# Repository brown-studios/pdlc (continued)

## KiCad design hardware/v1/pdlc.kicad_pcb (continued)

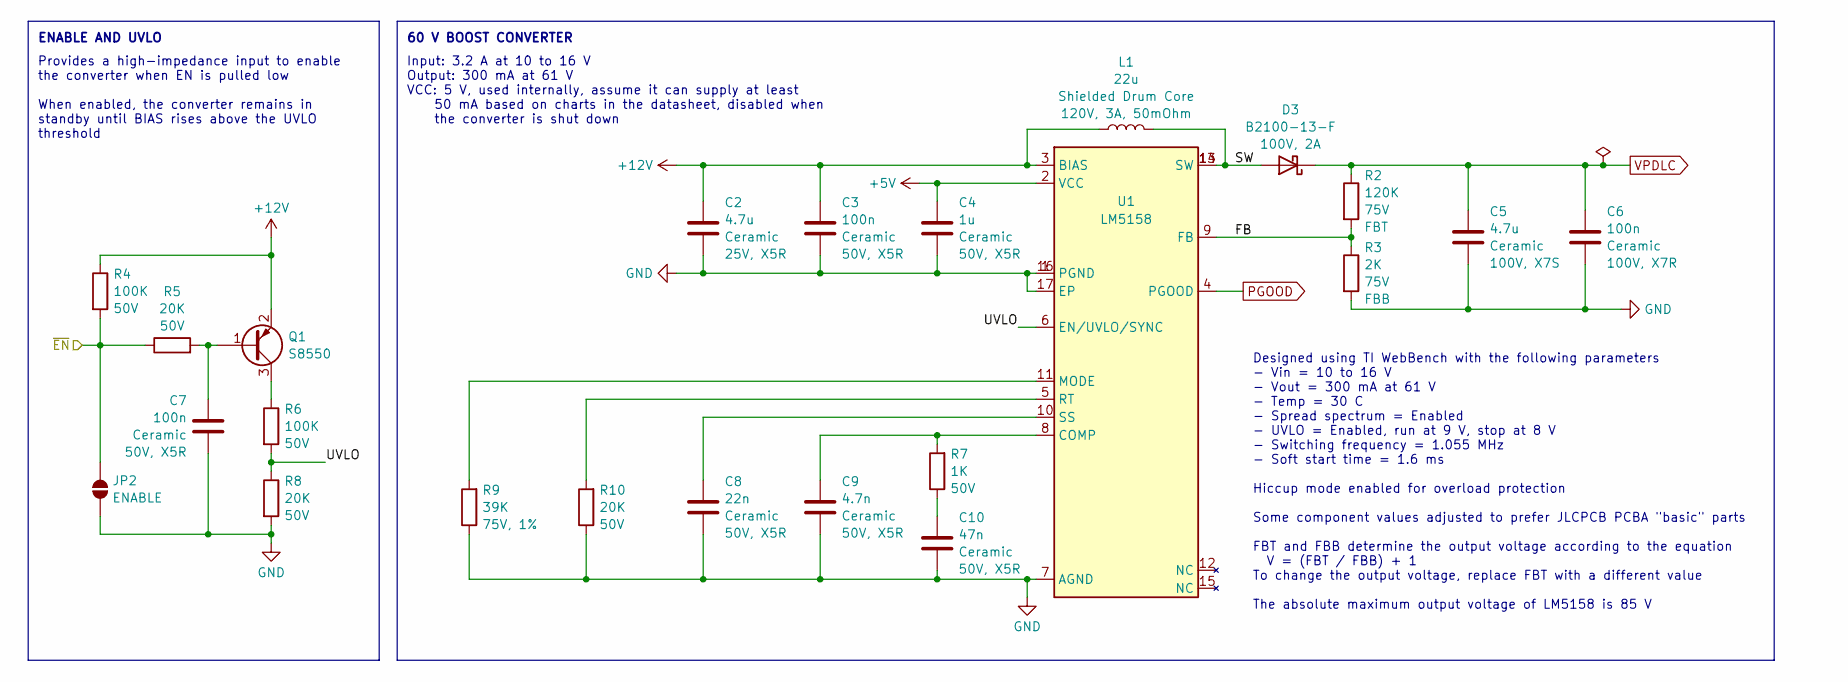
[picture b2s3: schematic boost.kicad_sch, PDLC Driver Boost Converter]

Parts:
C2: 4.7u; C_0805_2012Metric; Rating 25V, X5R; LCSC C1779
C3: 100n; C_0603_1608Metric; Rating 50V, X5R; LCSC C14663
C4: 1u; C_0603_1608Metric; Rating 50V, X5R; LCSC C15849
C5: 4.7u; C_1210_3225Metric; Rating 100V, X7S; LCSC C2803397
C6: 100n; C_0805_2012Metric; Rating 100V, X7R; LCSC C28233
C7: 100n; C_0402_1005Metric; Rating 50V, X5R; LCSC C307331
C8: 22n; C_0402_1005Metric; Rating 50V, X5R; LCSC C1532
C9: 4.7n; C_0402_1005Metric; Rating 50V, X5R; LCSC C1538
C10: 47n; C_0603_1608Metric; Rating 50V, X5R; LCSC C1622
D3: B2100-13-F; D_SMB; Rating 100V, 2A; LCSC C110479
JP2: SolderJumper_2_Open; SolderJumper-2_P1.3mm_Open_TrianglePad1.0x1.5mm
L1: 22u; WE-PD_1050P; Rating 120V, 3A, 50mOhm; Part 7447714220; LCSC C2651173
Q1: S8550; SOT-23; LCSC C105432
R2: 120K; R_0603_1608Metric; Rating 75V; LCSC C25808
R3: 2K; R_0603_1608Metric; Rating 75V; LCSC C22975
R4, R6: 100K; R_0402_1005Metric; Rating 50V; LCSC C25741
R5, R8, R10: 20K; R_0402_1005Metric; Rating 50V; LCSC C25765
R7: 1K; R_0402_1005Metric; Rating 50V; LCSC C11702
R9: 39K; R_0603_1608Metric; Rating 75V, 1%; LCSC C23153
U1: LM5158; LCSC C3188433

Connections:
+5V: C4.1, U1.2 (VCC); also elsewhere on the board
+12V: C2.1, C3.1, L1.1, Q1.2 (E), R4.1, U1.3 (BIAS); also elsewhere on the board
/boost/FB: R2.2, R3.1, U1.9 (FB)
/boost/SW: D3.2 (A), L1.2, U1.13 (SW), U1.14 (SW)
/boost/UVLO: R6.2, R8.1, U1.6 (EN/UVLO/SYNC)
/~EN: JP2.1 (A), R4.2, R5.1; also elsewhere on the board
GND: C2.2, C3.2, C4.2, C5.2, C6.2, C7.2, C8.2, C9.2, C10.2, JP2.2 (B), R3.2, R8.2, R9.1, R10.1, U1.1 (PGND), U1.7 (AGND), U1.16 (PGND), U1.17 (EP); also elsewhere on the board
unnamed: C10.1, R7.1
unnamed: C7.1, Q1.1 (B), R5.2
unnamed: Q1.3 (C), R6.1
unnamed: C9.1, R7.2, U1.8 (COMP)
unnamed: R9.2, U1.11 (MODE)
unnamed: R10.2, U1.5 (RT)
unnamed: C8.1, U1.10 (SS)
PGOOD: U1.4 (PGOOD); also elsewhere on the board
VPDLC: C5.1, C6.1, D3.1 (K), R2.1; also elsewhere on the board

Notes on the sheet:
60 V BOOST CONVERTER
Provides a high-impedance input to enable the converter when EN is pulled low When enabled, the converter remains in standby until BIAS rises above the UVLO threshold
Designed using TI WebBench with the following parameters - Vin = 10 to 16 V - Vout = 300 mA at 61 V - Temp = 30 C - Spread spectrum = Enabled - UVLO = Enabled, run at 9 V, stop at 8 V - Switching frequency = 1.055 MHz - Soft start time = 1.6 ms Hiccup mode enabled for overload protection Some compo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
ENABLE AND UVLO
Input: 3.2 A at 10 to 16 V Output: 300 mA at 61 V VCC: 5 V, used internally, assume it can supply at least 50 mA based on charts in the datasheet, disabled when the converter is shut down

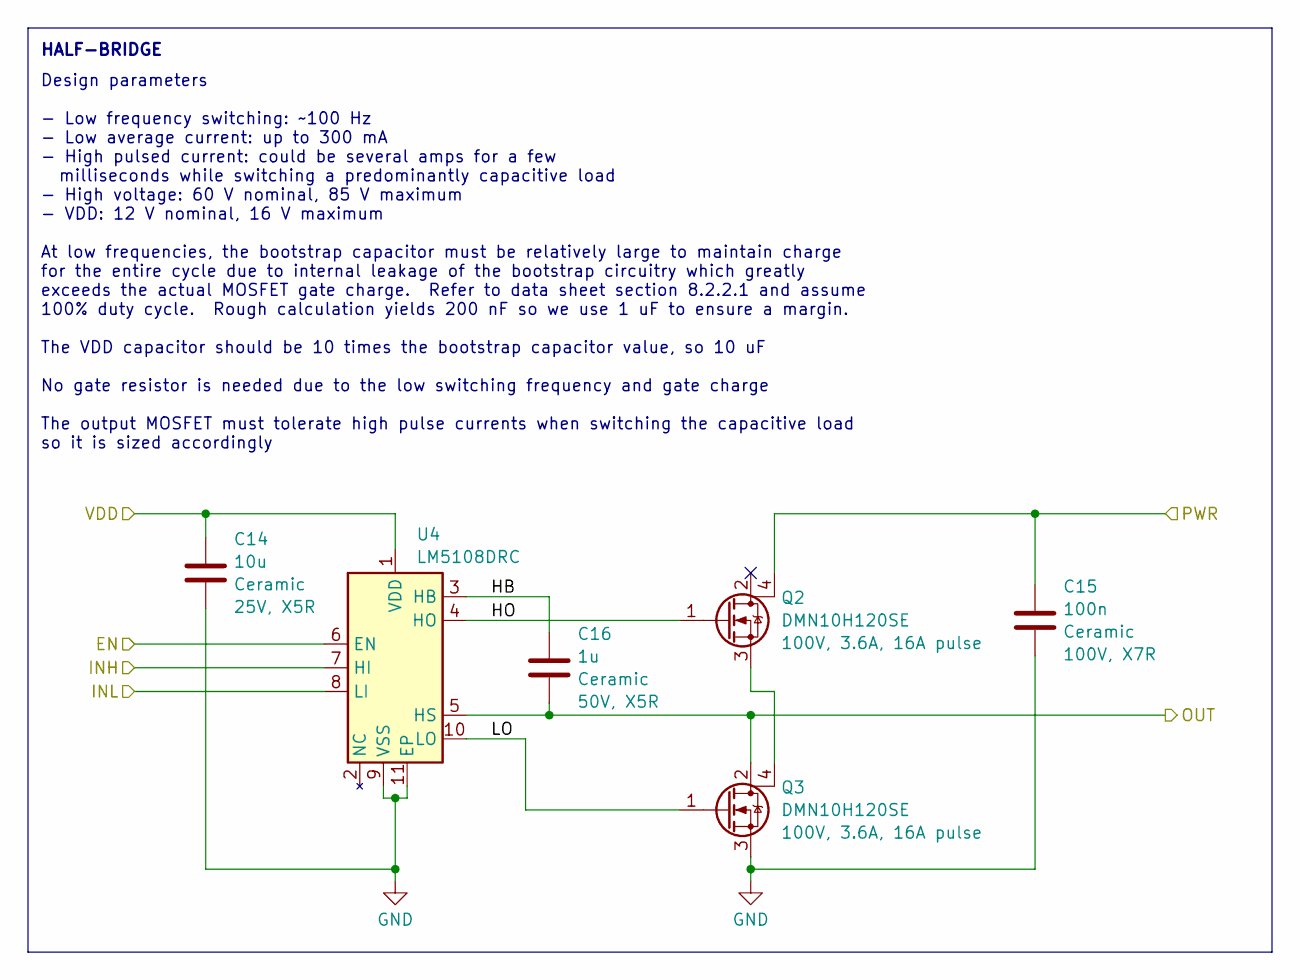
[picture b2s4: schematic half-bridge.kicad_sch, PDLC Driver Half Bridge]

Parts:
C14: 10u; C_0603_1608Metric; Rating 25V, X5R; LCSC C96446
C15: 100n; C_0805_2012Metric; Rating 100V, X7R; LCSC C28233
C16: 1u; C_0603_1608Metric; Rating 50V, X5R; LCSC C15849
Q2, Q3: DMN10H120SE; SOT-223; Rating 100V, 3.6A, 16A pulse; LCSC C460989
U4: LM5108DRC; VSON-10-1EP_3x3mm_P0.5mm_EP1.65x2.4mm; LCSC C2676946

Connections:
+12V: C14.1, U4.1 (VDD); also elsewhere on the board
/OUTA: C16.2, Q3.2 (D), U4.5 (HS); also elsewhere on the board
/inverter/PHASE: U4.8 (LI); also elsewhere on the board
/inverter/half-bridge A/EN: U4.6 (EN); also elsewhere on the board
/inverter/half-bridge A/HB: C16.1, U4.3 (HB)
/inverter/half-bridge A/HO: Q2.1 (G), U4.4 (HO)
/inverter/half-bridge A/LO: Q3.1 (G), U4.10 (LO)
/inverter/~PHASE: U4.7 (HI); also elsewhere on the board
GND: C14.2, C15.2, Q3.3 (S), U4.9 (VSS), U4.11 (EP); also elsewhere on the board
unnamed: Q2.3 (S), Q3.4 (D)
VPDLC: C15.1, Q2.4 (D); also elsewhere on the board

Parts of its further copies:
C17: 10u; C_0603_1608Metric; Rating 25V, X5R; LCSC C96446
C18: 100n; C_0805_2012Metric; Rating 100V, X7R; LCSC C28233
C19: 1u; C_0603_1608Metric; Rating 50V, X5R; LCSC C15849
Q4, Q5: DMN10H120SE; SOT-223; Rating 100V, 3.6A, 16A pulse; LCSC C460989
U5: LM5108DRC; VSON-10-1EP_3x3mm_P0.5mm_EP1.65x2.4mm; LCSC C2676946

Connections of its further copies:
+12V: C17.1, U5.1 (VDD); also elsewhere on the board
/OUTB: C19.2, Q5.2 (D), U5.5 (HS); also elsewhere on the board
/inverter/PHASE: U5.7 (HI); also elsewhere on the board
/inverter/half-bridge A/EN: U5.6 (EN); also elsewhere on the board
/inverter/half-bridge B/HB: C19.1, U5.3 (HB)
/inverter/half-bridge B/HO: Q4.1 (G), U5.4 (HO)
/inverter/half-bridge B/LO: Q5.1 (G), U5.10 (LO)
/inverter/~PHASE: U5.8 (LI); also elsewhere on the board
GND: C17.2, C18.2, Q5.3 (S), U5.9 (VSS), U5.11 (EP); also elsewhere on the board
unnamed: Q4.3 (S), Q5.4 (D)
VPDLC: C18.1, Q4.4 (D); also elsewhere on the board

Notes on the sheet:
Design parameters - Low frequency switching: ~100 Hz - Low average current: up to 300 mA - High pulsed current: could be several amps for a few milliseconds while switching a predominantly capacitive load - High voltage: 60 V nominal, 85 V maximum - VDD: 12 V nominal, 16 V maximum At low frequencie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
HALF-BRIDGE

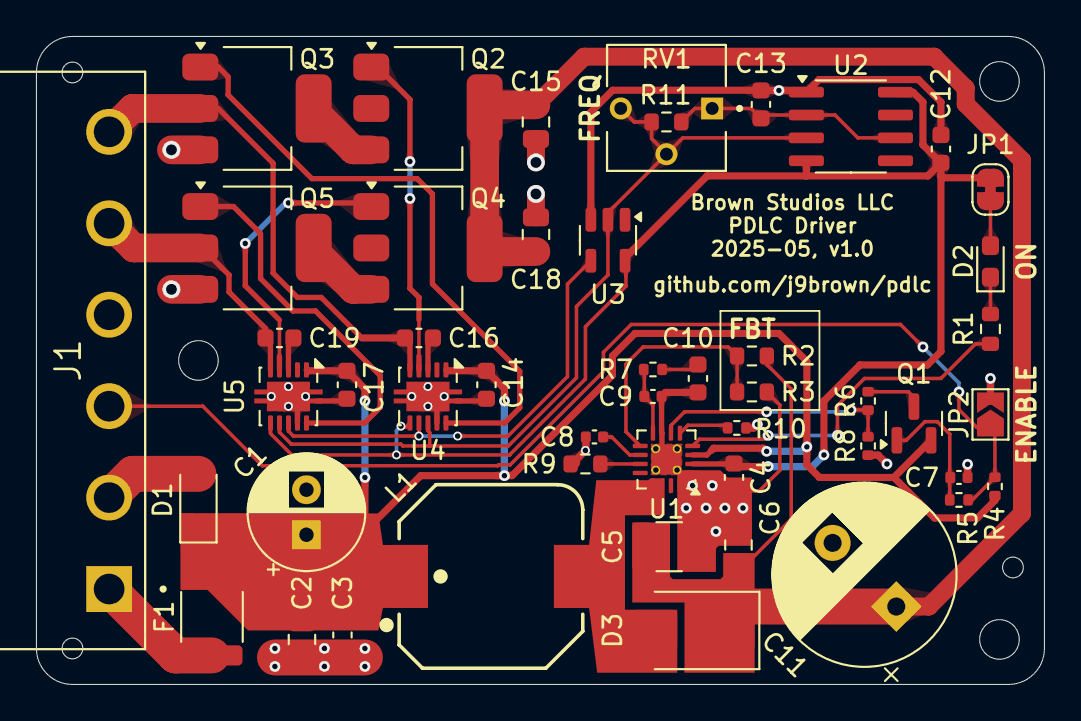
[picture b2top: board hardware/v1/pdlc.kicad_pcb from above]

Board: 2 copper layers, 56.0 x 36.0 mm, 56 parts (0 on the bottom side), 33 nets.

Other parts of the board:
H1, H1#2, H2: MountingHole_2.2mm_M2
TH1, TH3, TH4: JLCPCB_PCBA_Tooling_Hole

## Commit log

2026-01-08 Migrate old hardware to v1 folder.
2026-01-08 Partial draft of v2 hardware.
2026-01-15 Finalize for production of v2 revision.
2026-02-18 wip firmware
2026-02-19 Implement initial firmware for v2 hardware.
    Noted in errata that the PFM buck converter does not work in this
    application and must be replaced by an FPWM version although there are
    tradeoffs and the output stage is inefficient at low load.
    Generate complementary sine waves for the output using the DAC and DMA.
    Provide basic on-off control and status reporting, no menu system yet.
